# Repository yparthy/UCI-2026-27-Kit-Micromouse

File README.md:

# UCI Kit Mouse (2026-2027 Ver.)

## Team Infromation

**Team Name:** Team _____
**Member:** Parth Kansal
**Repository:** Practice Submission: Setup Project Environmnt

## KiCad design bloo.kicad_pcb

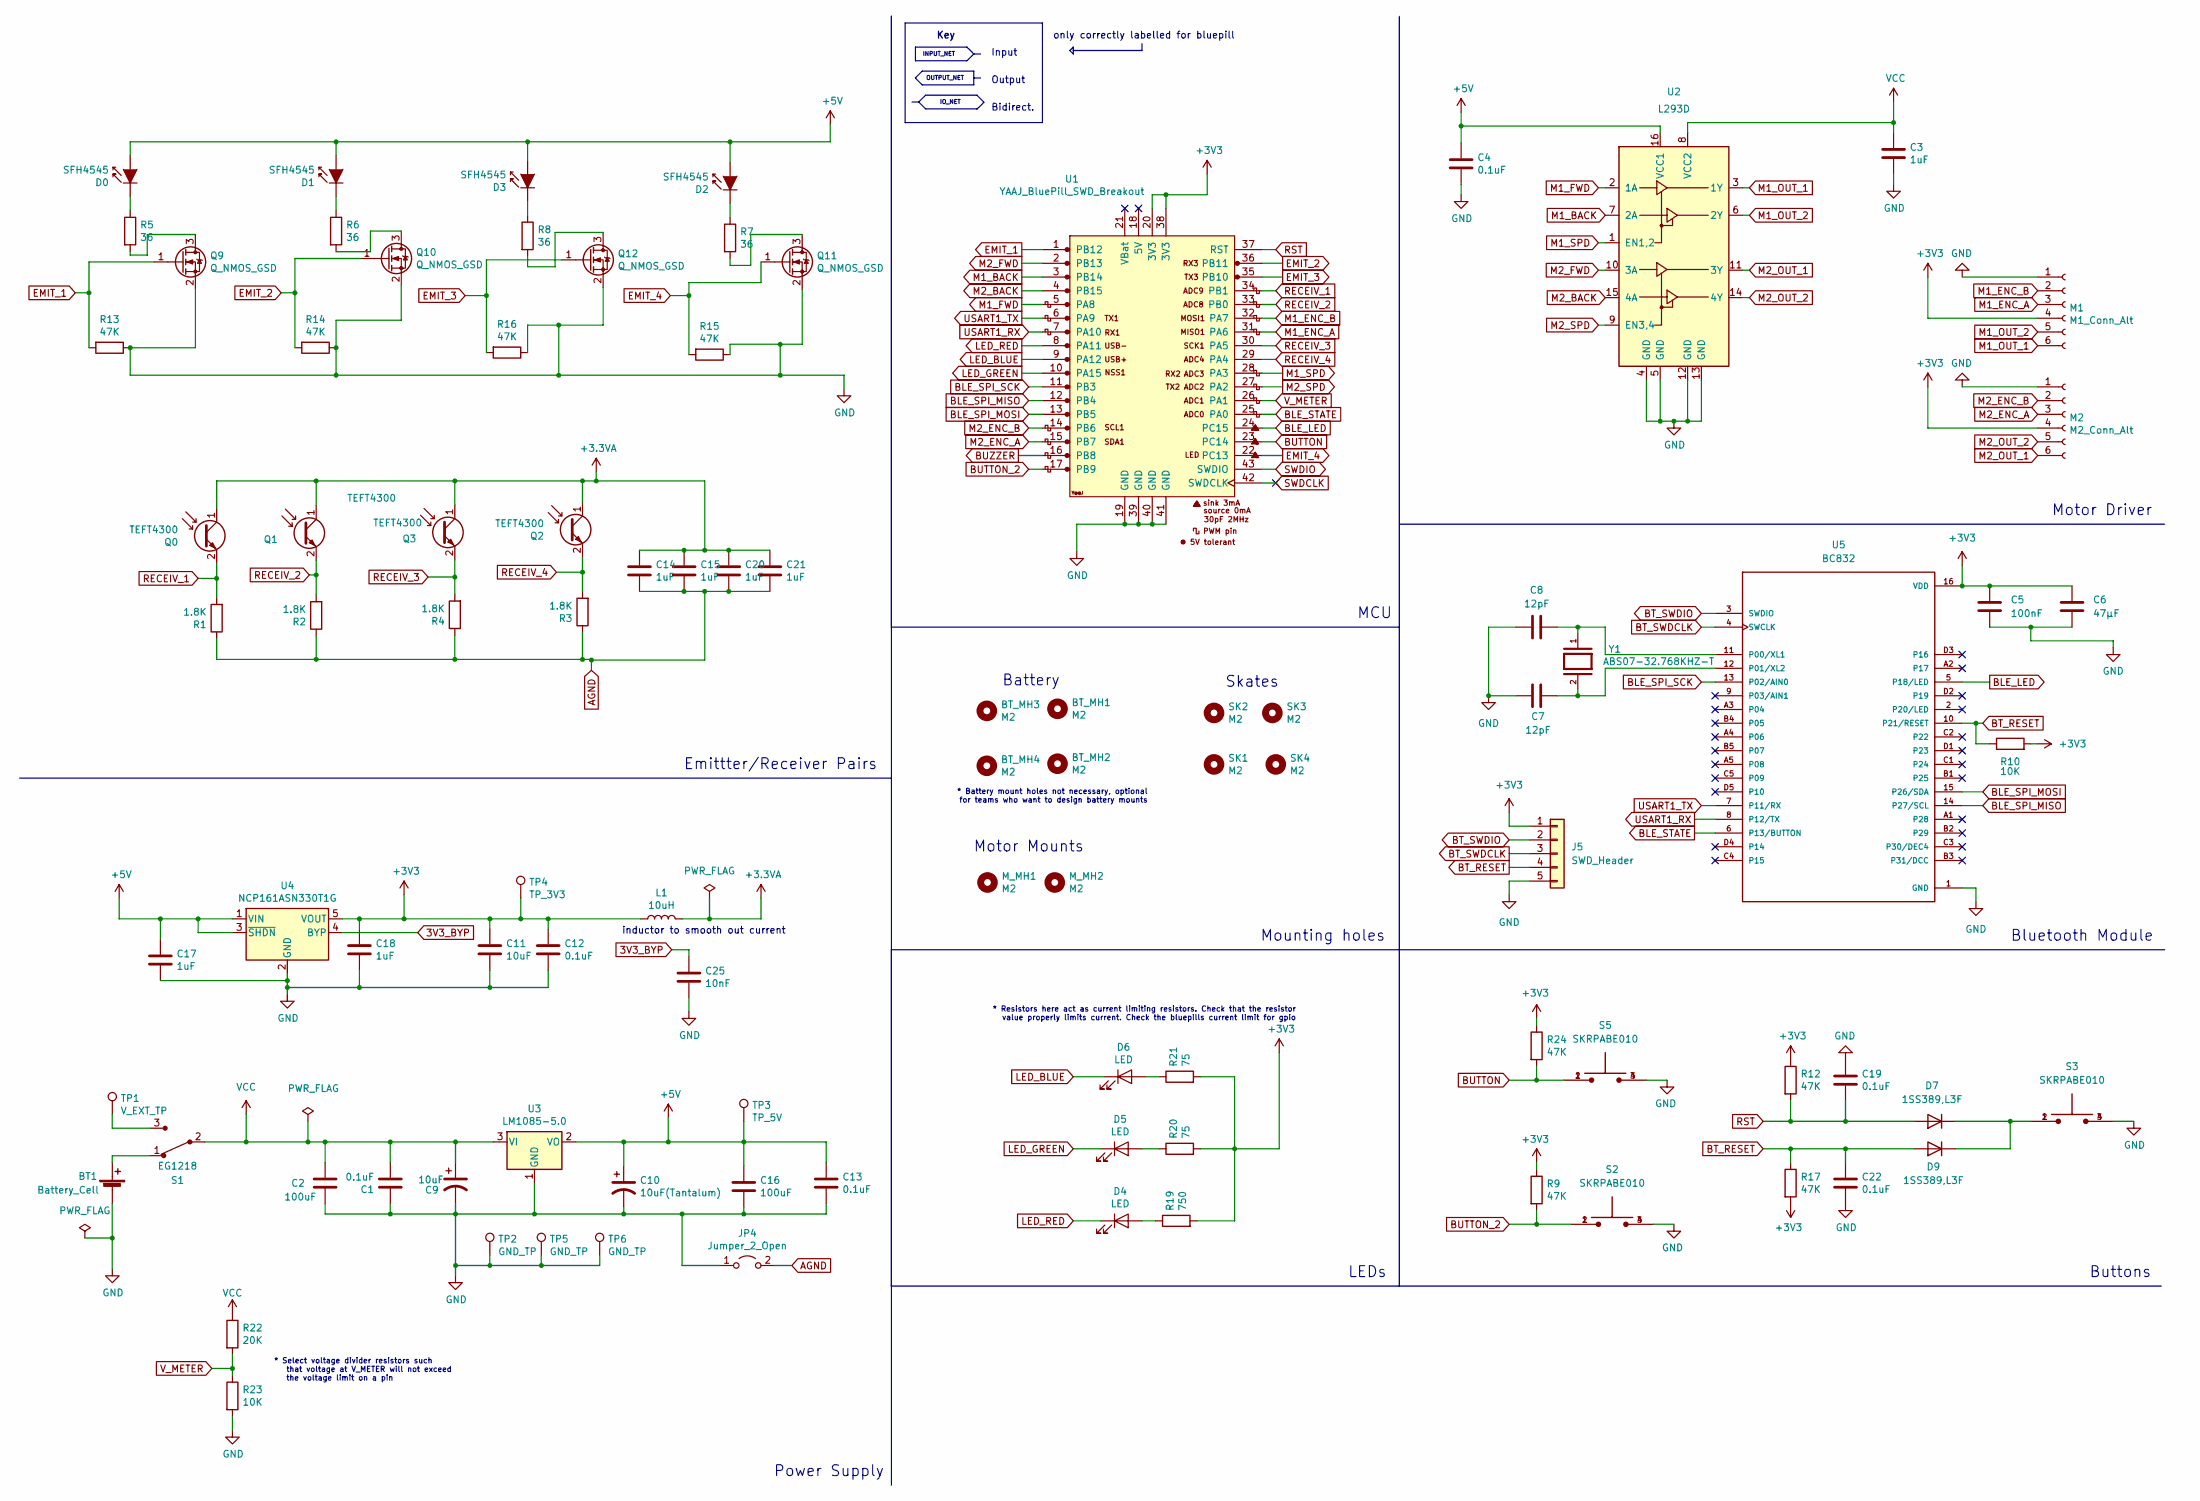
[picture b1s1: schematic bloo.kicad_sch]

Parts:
BT1: Battery_Cell; AMASS_XT30UPB-M_1x02_P5.0mm_Vertical; LCSC Part # C99101
BT_MH1, BT_MH2, BT_MH3, BT_MH4: M2; MountingHole_2.2mm_M2
C1, C4, C12, C13, C19, C22: 0.1uF; C_1206_3216Metric_Pad1.33x1.80mm_HandSolder; LCSC Part # C1945
C2, C16: 100uF; CP_Radial_D6.3mm_P2.50mm; LCSC Part # C1590882
C3, C14, C15, C17, C18, C20, C21: 1uF; C_1206_3216Metric_Pad1.33x1.80mm_HandSolder; LCSC Part # C28322
C5: 100nF; C_0603_1608Metric; LCSC Part # C1590
C6: 47µF; C_1206_3216Metric; LCSC Part # C68361
C7, C8: 12pF; C_0603_1608Metric_Pad1.08x0.95mm_HandSolder; LCSC Part # C38523
C9, C11: 10uF; C_1206_3216Metric_Pad1.33x1.80mm_HandSolder; LCSC Part # C39127
C10: 10uF(Tantalum); C_1206_3216Metric_Pad1.33x1.80mm_HandSolder; LCSC Part # C1952791
C25: 10nF; C_1206_3216Metric_Pad1.33x1.80mm_HandSolder; LCSC Part # C1846
D0, D1, D2, D3: SFH4545; Emitter; LCSC Part # C2900370
D4: LED; LED_0805_2012Metric_Pad1.15x1.40mm_HandSolder; LCSC Part # C5879380
D5: LED; LED_0805_2012Metric_Pad1.15x1.40mm_HandSolder; LCSC Part # C2890404
D6: LED; LED_0805_2012Metric_Pad1.15x1.40mm_HandSolder; LCSC Part # C2293
D7, D9: 1SS389,L3F; D_SOD-523; LCSC Part # C516855
J5: SWD_Header; PinHeader_1x05_P2.54mm_Vertical
JP4: Jumper_2_Open; SolderJumper-2_P1.3mm_Bridged_Pad1.0x1.5mm
L1: 10uH; L_1206_3216Metric_Pad1.42x1.75mm_HandSolder; LCSC Part # C845121
M1: M1_Conn_Alt; JST_SH_BM06B-SRSS-TB_1x06-1MP_P1.00mm_Vertical; LCSC Part # C144397
M2: M2_Conn_Alt; JST_SH_BM06B-SRSS-TB_1x06-1MP_P1.00mm_Vertical; LCSC Part # C144397
M_MH1, M_MH2: M2; Motor_mouse
Q0, Q1, Q2, Q3: TEFT4300; Emitter; LCSC Part # C118301
Q9, Q10, Q11, Q12: Q_NMOS_GSD; SOT-23; LCSC Part # C5310967
R1, R2, R3, R4: 1.8K; R_1206_3216Metric_Pad1.30x1.75mm_HandSolder; LCSC Part # C22108
R5, R6, R7, R8: 36; R_1206_3216Metric_Pad1.30x1.75mm_HandSolder; LCSC Part # C18006
R9, R12, R13, R14, R15, R16, R17, R24: 47K; R_1206_3216Metric_Pad1.30x1.75mm_HandSolder; LCSC Part # C25664
R10, R23: 10K; R_1206_3216Metric_Pad1.30x1.75mm_HandSolder; LCSC Part # C2479071
R19: 750; R_1206_3216Metric_Pad1.30x1.75mm_HandSolder; LCSC Part # C17985
R20, R21: 75; R_1206_3216Metric_Pad1.30x1.75mm_HandSolder; LCSC Part # C17987
R22: 20K; R_1206_3216Metric_Pad1.30x1.75mm_HandSolder; LCSC Part # C18003
S1: EG1218; MM Switch; MPN EG1218; Digi-Key_PN EG1903-ND
S2, S3, S5: SKRPABE010; SW4_SKRPABE010_ALPS; LCSC Part # C778166
SK1, SK2, SK3, SK4: M2; MountingHole_2.2mm_M2
TP1: V_EXT_TP; PinHeader_1x01_P2.54mm_Vertical
TP2, TP5, TP6: GND_TP; PinHeader_1x01_P2.54mm_Vertical
TP3: TP_5V; PinHeader_1x01_P2.54mm_Vertical
TP4: TP_3V3; PinHeader_1x01_P2.54mm_Vertical
U1: YAAJ_BluePill_SWD_Breakout; STM32F103
U2: L293D; DIP-16_W7.62mm; LCSC Part # C12340
U3: LM1085-5.0; 5V Voltage Reg; LCSC Part # C129950
U4: NCP161ASN330T1G; SOT-23-5; LCSC Part # C892187
U5: BC832; XCVR_BC832; PARTREV 2.02
Y1: ABS07-32.768KHZ-T; CAP_ABS07-32.768KHZ-T_ABR; PARTREV 08.19.15; LCSC Part # C130253

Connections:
3V3_BYP: C25.1, U4.4 (BYP)
+3.3VA: C14.1, C15.1, C20.1, C21.1, L1.2, Q0.1 (C), Q1.1 (C), Q2.1 (C), Q3.1 (C)
+3V3: C5.1, C6.1, C11.1, C12.1, C18.1, J5.1, L1.1, M1.4, M2.4, R9.1, R10.2, R12.1, R17.2, R19.2, R20.2, R21.2, R24.1, TP4.1 (1_1), U1.20 (3V3), U1.38 (3V3), U4.5 (VOUT), U5.16 (VDD)
+5V: C4.1, C10.1, C13.1, C16.1, C17.1, D0.2 (A), D1.2 (A), D2.2 (A), D3.2 (A), TP3.1 (1_1), U2.16 (VCC1), U3.2 (VO), U4.1 (VIN), U4.3 (~SHDN)
AGND: C14.2, C15.2, C20.2, C21.2, JP4.2 (B), R1.1, R2.1, R3.1, R4.1
BLE_LED: U1.24 (PC15), U5.5 (P18/LED)
BLE_SPI_MISO: U1.12 (PB4), U5.14 (P27/SCL)
BLE_SPI_MOSI: U1.13 (PB5), U5.15 (P26/SDA)
BLE_SPI_SCK: U1.11 (PB3), U5.13 (P02/AIN0)
BLE_STATE: U1.25 (PA0), U5.6 (P13/BUTTON)
BT_RESET: C22.1, D9.2 (A), J5.4, R10.1, R17.1, U5.10 (P21/RESET)
BT_SWDCLK: J5.3, U5.4 (SWCLK)
BT_SWDIO: J5.2, U5.3 (SWDIO)
BUTTON: R24.2, S5.1, S5.2, U1.23 (PC14)
BUTTON_2: R9.2, S2.1, S2.2, U1.17 (PB9)
BUZZER: U1.16 (PB8)
EMIT_1: Q9.1 (G), R13.2, U1.1 (PB12)
EMIT_2: Q10.1 (G), R14.2, U1.36 (PB11)
EMIT_3: Q12.1 (G), R16.2, U1.35 (PB10)
EMIT_4: Q11.1 (G), R15.2, U1.22 (PC13)
GND: BT1.2 (-), C1.1, C2.2, C3.2, C4.2, C5.2, C6.2, C7.1, C8.1, C9.2, C10.2, C11.2, C12.2, C13.2, C16.2, C17.2, C18.2, C19.1, C22.2, C25.2, J5.5, JP4.1 (A), M1.1, M2.1, Q9.2 (S), Q10.2 (S), Q11.2 (S), Q12.2 (S), R13.1, R14.1, R15.1, R16.1, R23.2, S2.3, S2.4, S3.3, S3.4, S5.3, S5.4, TP2.1 (1_1), TP5.1 (1_1), TP6.1 (1_1), U1.19 (GND), U1.39 (GND), U1.40 (GND), U1.41 (GND), U2.4 (GND), U2.5 (GND), U2.12 (GND), U2.13 (GND), U3.1 (GND), U4.2 (GND), U5.1 (GND)
LED_BLUE: D6.1 (K), U1.9 (PA12)
LED_GREEN: D5.1 (K), U1.10 (PA15)
LED_RED: D4.1 (K), U1.8 (PA11)
M1_BACK: U1.3 (PB14), U2.7 (2A)
M1_ENC_A: M1.3, U1.31 (PA6)
M1_ENC_B: M1.2, U1.32 (PA7)
M1_FWD: U1.5 (PA8), U2.2 (1A)
M1_OUT_1: M1.6, U2.3 (1Y)
M1_OUT_2: M1.5, U2.6 (2Y)
M1_SPD: U1.28 (PA3), U2.1 (EN1,2)
M2_BACK: U1.4 (PB15), U2.15 (4A)
M2_ENC_A: M2.3, U1.15 (PB7)
M2_ENC_B: M2.2, U1.14 (PB6)
M2_FWD: U1.2 (PB13), U2.10 (3A)
M2_OUT_1: M2.6, U2.11 (3Y)
M2_OUT_2: M2.5, U2.14 (4Y)
M2_SPD: U1.27 (PA2), U2.9 (EN3,4)
unnamed: BT1.1 (+), S1.1
unnamed: D0.1 (K), R5.1
unnamed: D1.1 (K), R6.1
unnamed: D2.1 (K), R7.1
unnamed: D3.1 (K), R8.1
unnamed: D4.2 (A), R19.1
unnamed: D5.2 (A), R20.1
unnamed: D6.2 (A), R21.1
unnamed: D7.1 (K), D9.1 (K), S3.1, S3.2
unnamed: Q9.3 (D), R5.2
unnamed: Q10.3 (D), R6.2
unnamed: Q11.3 (D), R7.2
unnamed: Q12.3 (D), R8.2
unnamed: S1.3, TP1.1 (1_1)
unnamed: C8.2, U5.11 (P00/XL1), Y1.1
unnamed: C7.2, U5.12 (P01/XL2), Y1.2
RECEIV_1: Q0.2 (E), R1.2, U1.34 (PB1)
RECEIV_2: Q1.2 (E), R2.2, U1.33 (PB0)
RECEIV_3: Q3.2 (E), R4.2, U1.30 (PA5)
RECEIV_4: Q2.2 (E), R3.2, U1.29 (PA4)
RST: C19.2, D7.2 (A), R12.2, U1.37 (RST)
USART1_RX: U1.7 (PA10), U5.8 (P12/TX)
USART1_TX: U1.6 (PA9), U5.7 (P11/RX)
VCC: C1.2, C2.1, C3.1, C9.1, R22.1, S1.2, U2.8 (VCC2), U3.3 (VI)
V_METER: R22.2, R23.1, U1.26 (PA1)

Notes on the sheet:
Mounting holes
Bluetooth Module
Output
IO_NET
Battery
Input
inductor to smooth out current
* Battery mount holes not necessary, optional for teams who want to design battery mounts
Motor Driver
Emittter/Receiver Pairs
* Resistors here act as current limiting resistors. Check that the resistor value properly limits current. Check the bluepills current limit for gpio
LEDs
Bidirect.
MCU
OUTPUT_NET
only correctly labelled for bluepill
* Select voltage divider resistors such that voltage at V_METER will not exceed the voltage limit on a pin
Motor Mounts
Buttons
Skates
Power Supply
Key
INPUT_NET

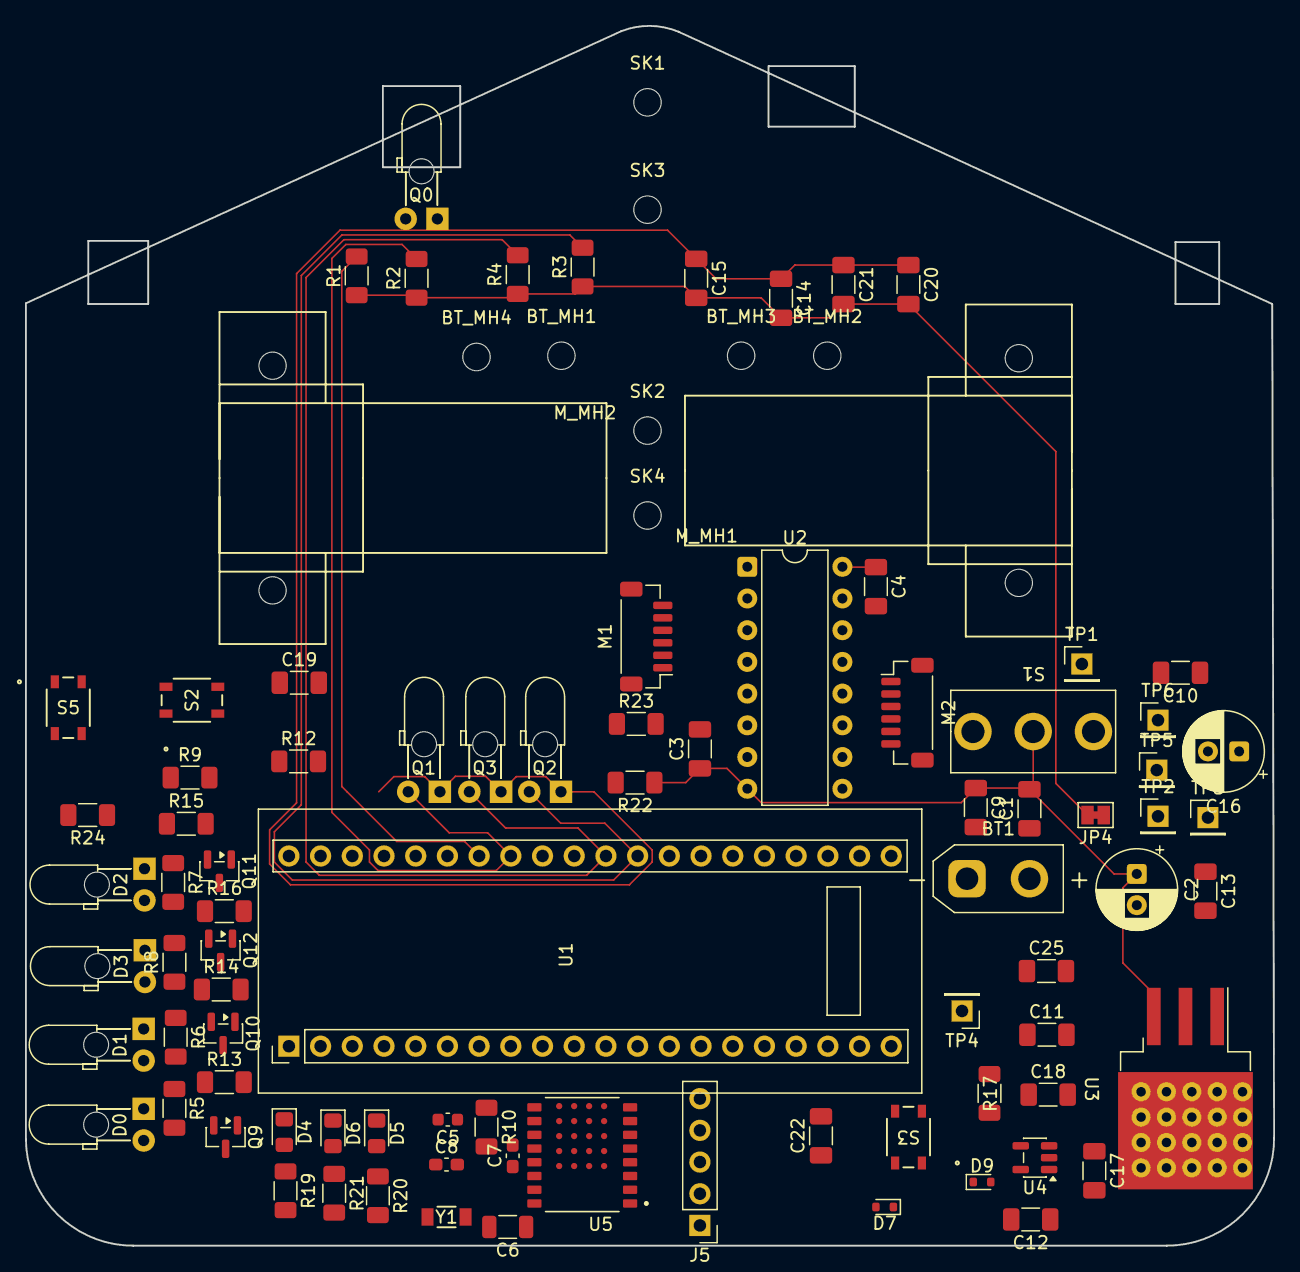
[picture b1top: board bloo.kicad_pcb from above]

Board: 2 copper layers, 100.0 x 97.7 mm, 93 parts (0 on the bottom side), 62 nets.
